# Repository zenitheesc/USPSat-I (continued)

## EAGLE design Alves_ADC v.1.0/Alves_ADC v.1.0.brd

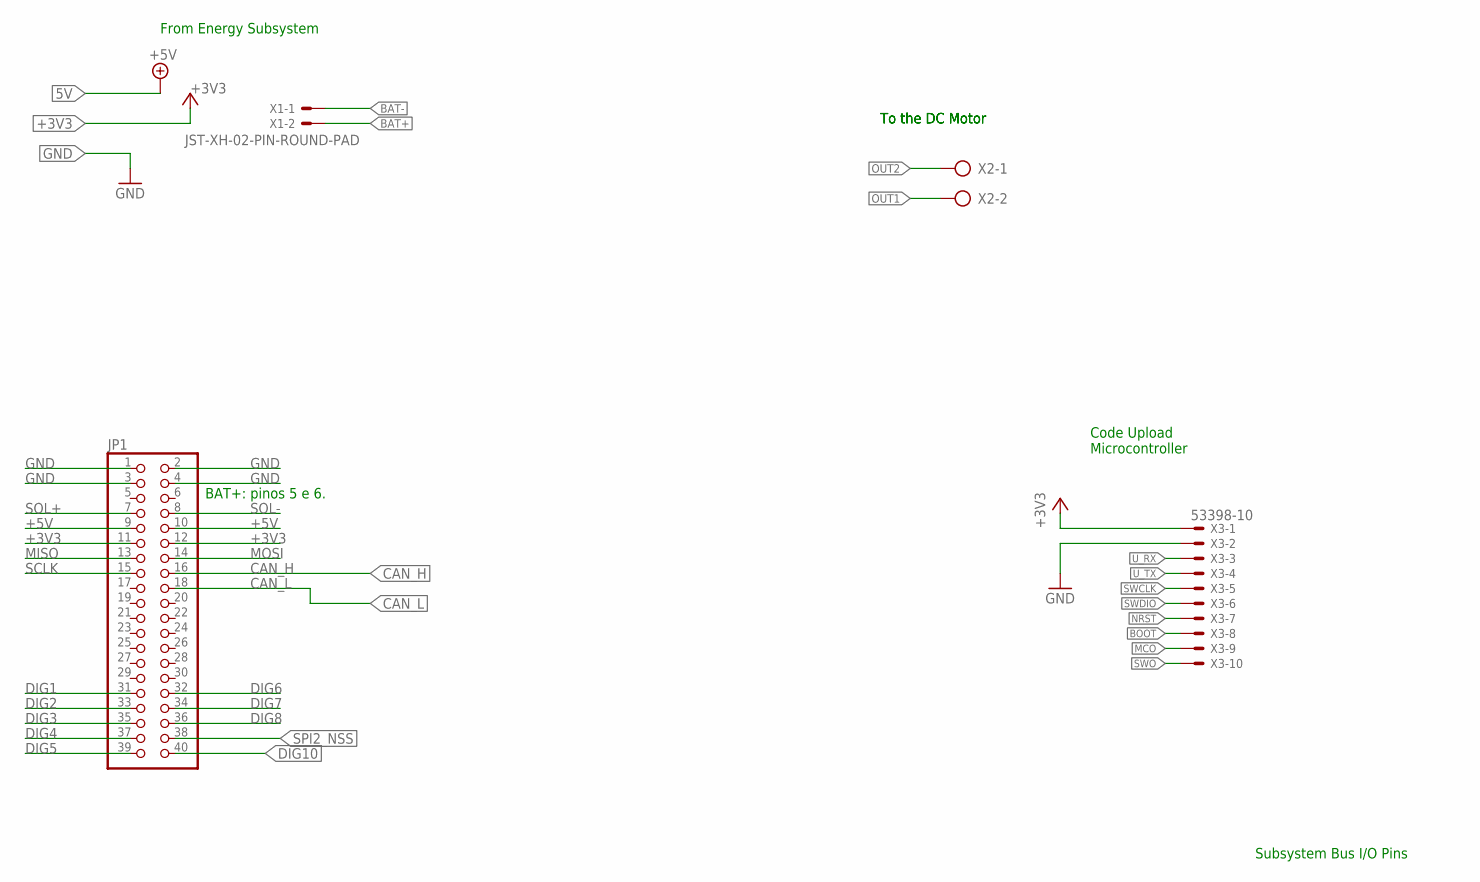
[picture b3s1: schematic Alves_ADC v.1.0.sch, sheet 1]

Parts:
JP1: PINHD-2X20; 2X20
X1: JST-XH-02-PIN-ROUND-PAD; JST-XH-02-PACKAGE-ROUND-PAD
X2: AK500/2
X3: 53398-10

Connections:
+3V3: JP1.11, JP1.12, X3.1; also elsewhere on the board
+5V: JP1.9, JP1.10; also elsewhere on the board
BAT+: X1.2; also elsewhere on the board
BAT-: X1.1; also elsewhere on the board
BOOT: X3.8; also elsewhere on the board
CAN_H: JP1.16; also elsewhere on the board
CAN_L: JP1.18; also elsewhere on the board
DIG1: JP1.31
DIG2: JP1.33
DIG3: JP1.35
DIG4: JP1.37
DIG5: JP1.39
DIG6: JP1.32
DIG7: JP1.34
DIG8: JP1.36
DIG10: JP1.40; also elsewhere on the board
GND: JP1.1, JP1.2, JP1.3, JP1.4, X3.2; also elsewhere on the board
MCO: X3.9; also elsewhere on the board
MISO: JP1.13; also elsewhere on the board
MOSI: JP1.14; also elsewhere on the board
NRST: X3.7; also elsewhere on the board
OUT1: X2.2; also elsewhere on the board
OUT2: X2.1; also elsewhere on the board
SCLK: JP1.15; also elsewhere on the board
SOL+: JP1.7
SOL-: JP1.8
SPI2_NSS: JP1.38; also elsewhere on the board
SWCLK: X3.5; also elsewhere on the board
SWDIO: X3.6; also elsewhere on the board
SWO: X3.10; also elsewhere on the board
U_RX: X3.3; also elsewhere on the board
U_TX: X3.4; also elsewhere on the board

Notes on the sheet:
Subsystem Bus I/O Pins
From Energy Subsystem
To the DC Motor
Code Upload Microcontroller
BAT+: pinos 5 e 6.

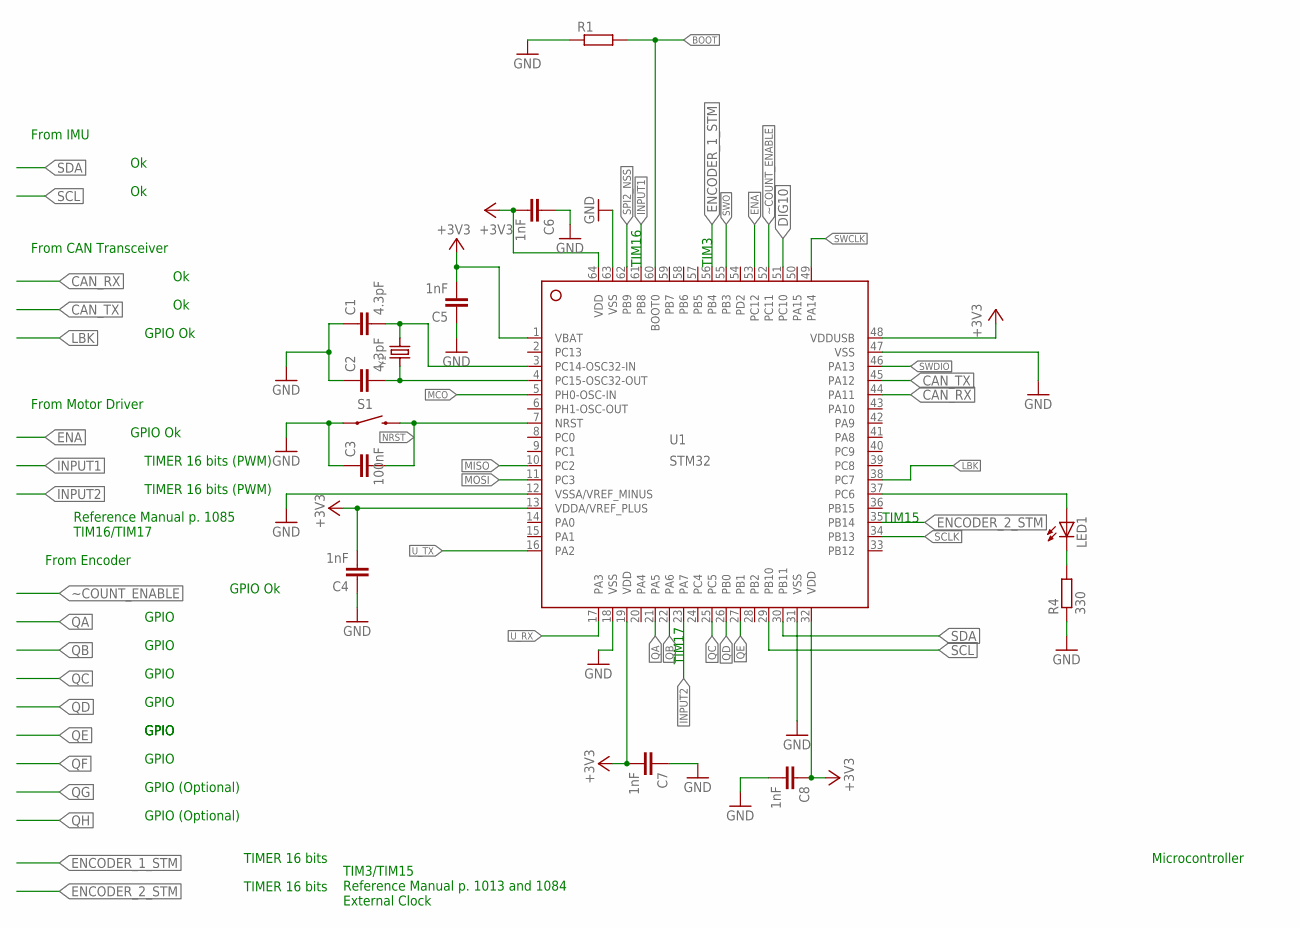
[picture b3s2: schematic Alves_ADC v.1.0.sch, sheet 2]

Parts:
C1, C2: 4.3pF; C1206
C3: 100nF; C1206
C4, C5, C6, C7, C8: 1nF; C1206
LED1: LEDSMT1206; 1206
R1: R-EU_R1206; R1206
R4: 330; R1206
S1: SWITCH-MOMENTARY-2SMD-1101NE; TACTILE-SWITCH-1101NE
U1: STM32; LQFP64_10X10
Y1: CRYSTAL8X3.8SMT; CRYSTAL_8X3.8

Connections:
+3V3: C4.2, C5.2, C6.2, C7.2, C8.1, U1.1 (VBAT), U1.13 (VDDA/VREF_PLUS), U1.19 (VDD), U1.32 (VDD), U1.48 (VDDUSB), U1.64 (VDD); also elsewhere on the board
BOOT: R1.2, U1.60 (BOOT0); also elsewhere on the board
CAN_RX: U1.44 (PA11); also elsewhere on the board
CAN_TX: U1.45 (PA12); also elsewhere on the board
DIG10: U1.51 (PC10); also elsewhere on the board
ENA: U1.53 (PC12); also elsewhere on the board
ENCODER_1_STM: U1.56 (PB4); also elsewhere on the board
ENCODER_2_STM: U1.35 (PB14); also elsewhere on the board
GND: C1.1, C2.1, C3.1, C4.1, C5.1, C6.1, C7.1, C8.2, R1.1, R4.1, S1.1, U1.12 (VSSA/VREF_MINUS), U1.18 (VSS), U1.31 (VSS), U1.47 (VSS), U1.63 (VSS); also elsewhere on the board
INPUT1: U1.61 (PB8); also elsewhere on the board
INPUT2: U1.23 (PA7); also elsewhere on the board
LBK: U1.38 (PC7); also elsewhere on the board
MCO: U1.5 (PH0-OSC-IN); also elsewhere on the board
MISO: U1.10 (PC2); also elsewhere on the board
MOSI: U1.11 (PC3); also elsewhere on the board
unnamed: LED1.A, U1.37 (PC6)
unnamed: C1.2, U1.3 (PC14-OSC32-IN), Y1.P$4 (2)
unnamed: C2.2, U1.4 (PC15-OSC32-OUT), Y1.P$1 (1)
unnamed: LED1.C, R4.2
NRST: C3.2, S1.2, U1.7 (NRST); also elsewhere on the board
QA: U1.21 (PA5); also elsewhere on the board
QB: U1.22 (PA6); also elsewhere on the board
QC: U1.25 (PC5); also elsewhere on the board
QD: U1.26 (PB0); also elsewhere on the board
QE: U1.27 (PB1); also elsewhere on the board
SCL: U1.29 (PB10); also elsewhere on the board
SCLK: U1.34 (PB13); also elsewhere on the board
SDA: U1.30 (PB11); also elsewhere on the board
SPI2_NSS: U1.62 (PB9); also elsewhere on the board
SWCLK: U1.49 (PA14); also elsewhere on the board
SWDIO: U1.46 (PA13); also elsewhere on the board
SWO: U1.55 (PB3); also elsewhere on the board
U_RX: U1.17 (PA3); also elsewhere on the board
U_TX: U1.16 (PA2); also elsewhere on the board
~COUNT_ENABLE: U1.52 (PC11); also elsewhere on the board

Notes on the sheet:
Microcontroller
From IMU
From Motor Driver
From CAN Transceiver
From Encoder
GPIO Ok
TIMER 16 bits (PWM)
TIMER 16 bits
GPIO (Optional)
Reference Manual p. 1085 TIM16/TIM17
TIM3/TIM15 Reference Manual p. 1013 and 1084 External Clock
TIM15
TIM17
TIM16
TIM3
GPIO

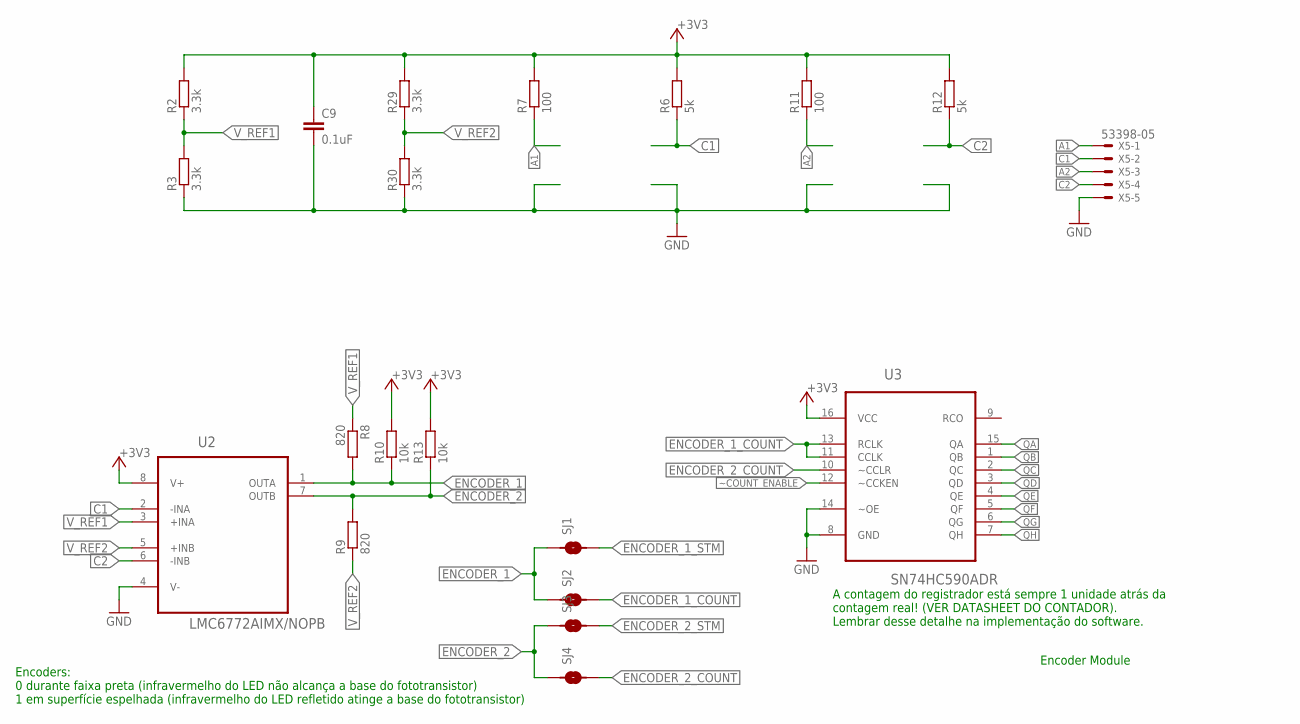
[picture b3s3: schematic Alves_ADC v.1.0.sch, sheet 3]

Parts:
C9: 0.1uF; C1206
R2, R3, R29, R30: 3.3k; R1206
R6, R12: 5k; R1206
R7, R11: 100; R1206
R8, R9: 820; R1206
R10, R13: 10k; R1206
SJ1, SJ2, SJ3, SJ4: SMD-JUMPER-2
U2: LMC6772AIMX/NOPB; SOIC127P600X175-8N
U3: SN74HC590ADR; SOIC127P600X175-16N
X5: 53398-05

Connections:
+3V3: C9.1, R2.2, R6.2, R7.2, R10.2, R11.2, R12.2, R13.2, R29.2, U2.8 (V+), U3.16 (VCC); also elsewhere on the board
A1: R7.1, X5.1
A2: R11.1, X5.3
C1: R6.1, U2.2 (-INA), X5.2
C2: R12.1, U2.6 (-INB), X5.4
ENCODER_1: R8.2, R10.1, SJ1.1, SJ2.1, U2.1 (OUTA)
ENCODER_1_COUNT: SJ2.2, U3.11 (CCLK), U3.13 (RCLK)
ENCODER_1_STM: SJ1.2; also elsewhere on the board
ENCODER_2: R9.2, R13.1, SJ3.1, SJ4.1, U2.7 (OUTB)
ENCODER_2_COUNT: SJ4.2, U3.10 (~CCLR)
ENCODER_2_STM: SJ3.2; also elsewhere on the board
GND: C9.2, R3.1, R30.1, U2.4 (V-), U3.8 (GND), U3.14 (~OE), X5.5; also elsewhere on the board
QA: U3.15 (QA); also elsewhere on the board
QB: U3.1 (QB); also elsewhere on the board
QC: U3.2 (QC); also elsewhere on the board
QD: U3.3 (QD); also elsewhere on the board
QE: U3.4 (QE); also elsewhere on the board
QF: U3.5 (QF)
QG: U3.6 (QG)
QH: U3.7 (QH)
V_REF1: R2.1, R3.2, R8.1, U2.3 (+INA)
V_REF2: R9.1, R29.1, R30.2, U2.5 (+INB)
~COUNT_ENABLE: U3.12 (~CCKEN); also elsewhere on the board

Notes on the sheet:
Encoder Module
Encoders: 0 durante faixa preta (infravermelho do LED não alcança a base do fototransistor) 1 em superfície espelhada (infravermelho do LED refletido atinge a base do fototransistor)
A contagem do registrador está sempre 1 unidade atrás da contagem real! (VER DATASHEET DO CONTADOR). Lembrar desse detalhe na implementação do software.

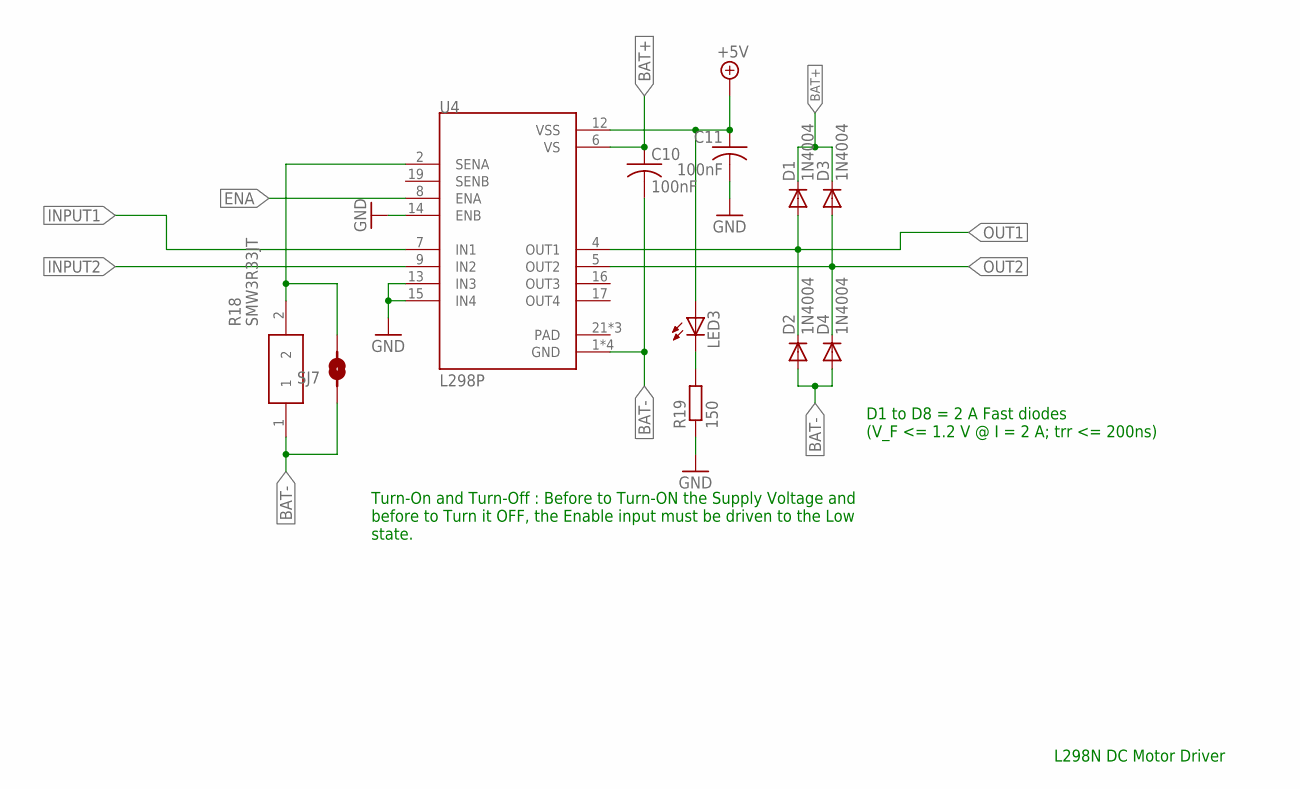
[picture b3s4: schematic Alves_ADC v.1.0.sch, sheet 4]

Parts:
C10, C11: 100nF; C050-024X044
D1, D2, D3, D4: 1N4004; DO41-10
LED3: LEDSMT1206; 1206
R18: SMW3R33JT; RESM12055X530N
R19: 150; R1206
SJ7: SMD-JUMPER-2
U4: L298P; SOIC127P1420X360-20N

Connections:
+5V: C11.1, LED3.A, U4.12 (VSS); also elsewhere on the board
BAT+: C10.1, D1.C, D3.C, U4.6 (VS); also elsewhere on the board
BAT-: C10.2, D2.A, D4.A, R18.1, SJ7.1, U4.1 (GND), U4.10 (GND), U4.11 (GND), U4.20 (GND); also elsewhere on the board
ENA: U4.8 (ENA); also elsewhere on the board
GND: C11.2, R19.1, U4.13 (IN3), U4.14 (ENB), U4.15 (IN4); also elsewhere on the board
INPUT1: U4.7 (IN1); also elsewhere on the board
INPUT2: U4.9 (IN2); also elsewhere on the board
unnamed: LED3.C, R19.2
unnamed: R18.2, SJ7.2, U4.2 (SENA)
OUT1: D1.A, D2.C, U4.4 (OUT1); also elsewhere on the board
OUT2: D3.A, D4.C, U4.5 (OUT2); also elsewhere on the board

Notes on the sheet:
L298N DC Motor Driver
D1 to D8 = 2 A Fast diodes (V_F <= 1.2 V @ I = 2 A; trr <= 200ns)
Turn-On and Turn-Off : Before to Turn-ON the Supply Voltage and before to Turn it OFF, the Enable input must be driven to the Low state.

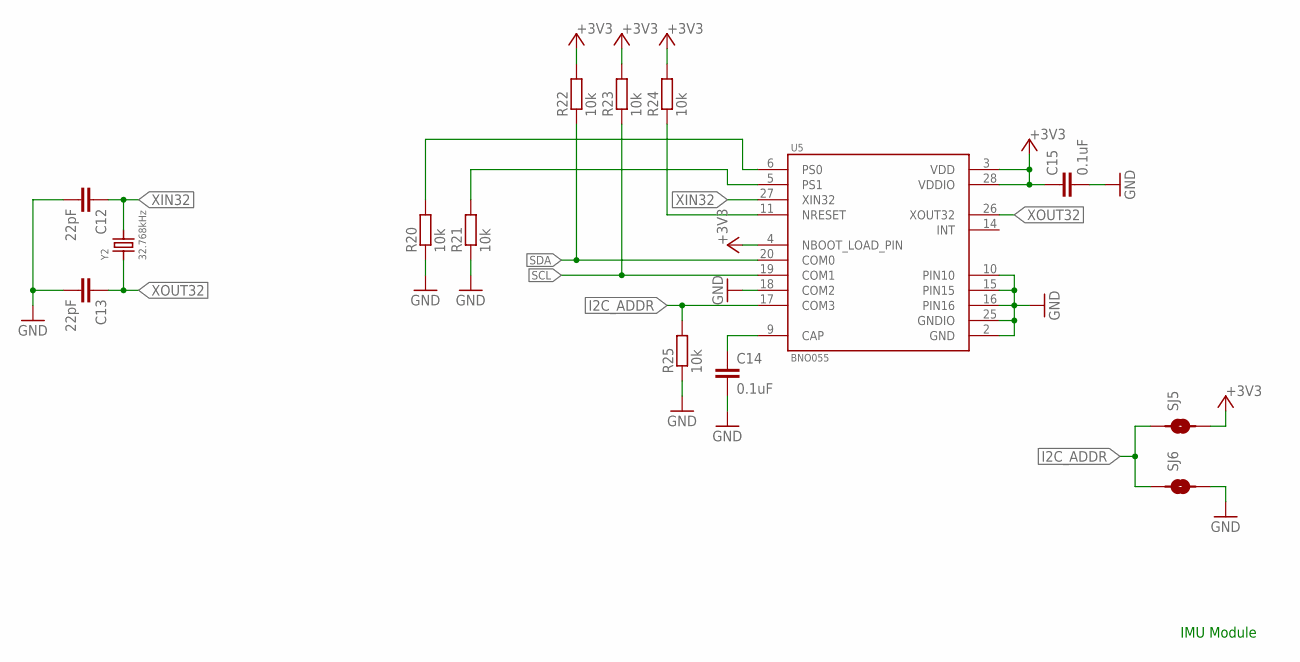
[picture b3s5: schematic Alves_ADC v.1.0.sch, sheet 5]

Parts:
C12, C13: 22pF; C1206
C14, C15: 0.1uF; C1206
R20, R21, R22, R23, R24, R25: 10k; R1206
SJ5, SJ6: SMD-JUMPER-2
U5: BNO055; LGA28R50P4X10_380X520X100
Y2: 32.768kHz; CRYSTAL_8X3.8

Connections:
+3V3: C15.1, R22.2, R23.2, R24.2, SJ5.2, U5.3 (VDD), U5.4 (NBOOT_LOAD_PIN), U5.28 (VDDIO); also elsewhere on the board
GND: C12.2, C13.2, C14.2, C15.2, R20.1, R21.1, R25.1, SJ6.2, U5.2 (GND), U5.10 (PIN10), U5.15 (PIN15), U5.16 (PIN16), U5.18 (COM2), U5.25 (GNDIO); also elsewhere on the board
I2C_ADDR: R25.2, SJ5.1, SJ6.1, U5.17 (COM3)
unnamed: C14.1, U5.9 (CAP)
NRESET: R24.1, U5.11 (NRESET)
PS0: R20.2, U5.6 (PS0)
PS1: R21.2, U5.5 (PS1)
SCL: R23.1, U5.19 (COM1); also elsewhere on the board
SDA: R22.1, U5.20 (COM0); also elsewhere on the board
XIN32: C12.1, U5.27 (XIN32), Y2.P$4 (2)
XOUT32: C13.1, U5.26 (XOUT32), Y2.P$1 (1)

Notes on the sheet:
IMU Module

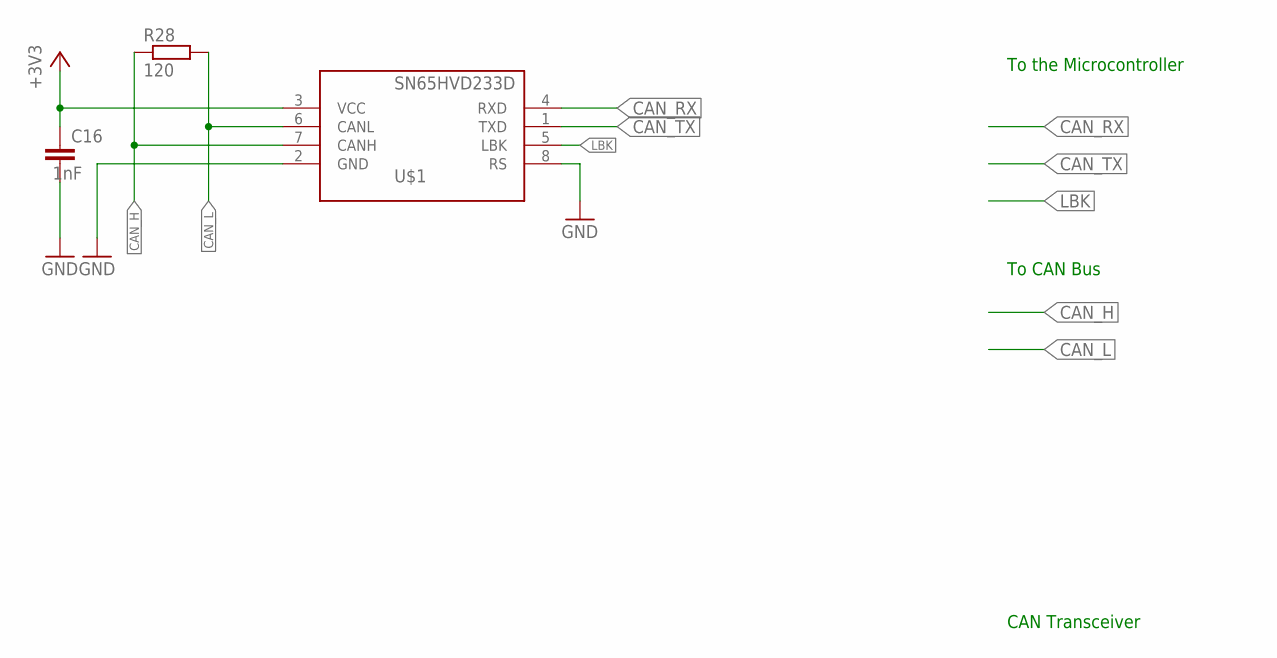
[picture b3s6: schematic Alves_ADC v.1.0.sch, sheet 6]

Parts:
C16: 1nF; C1206
R28: 120; R1206
U$1: SN65HVD233D; SOIC8

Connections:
+3V3: C16.1, U$1.3 (VCC); also elsewhere on the board
CAN_H: R28.1, U$1.7 (CANH); also elsewhere on the board
CAN_L: R28.2, U$1.6 (CANL); also elsewhere on the board
CAN_RX: U$1.4 (RXD); also elsewhere on the board
CAN_TX: U$1.1 (TXD); also elsewhere on the board
GND: C16.2, U$1.2 (GND), U$1.8 (RS); also elsewhere on the board
LBK: U$1.5 (LBK); also elsewhere on the board

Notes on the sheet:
CAN Transceiver
To the Microcontroller
To CAN Bus

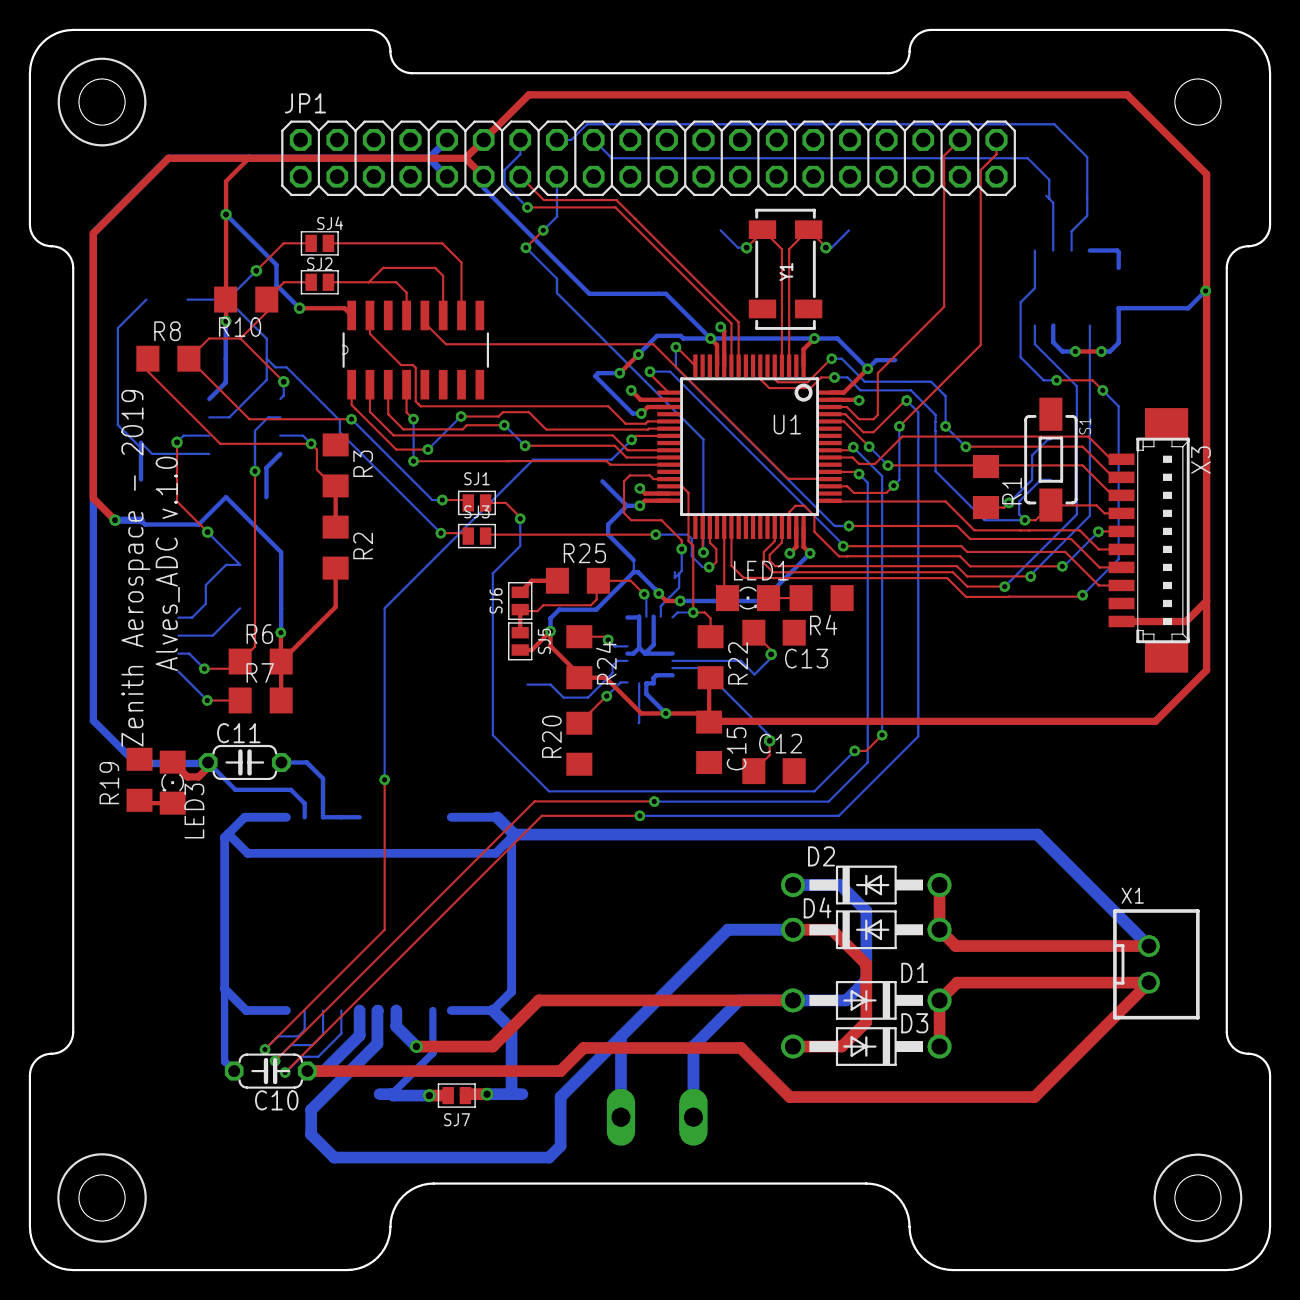
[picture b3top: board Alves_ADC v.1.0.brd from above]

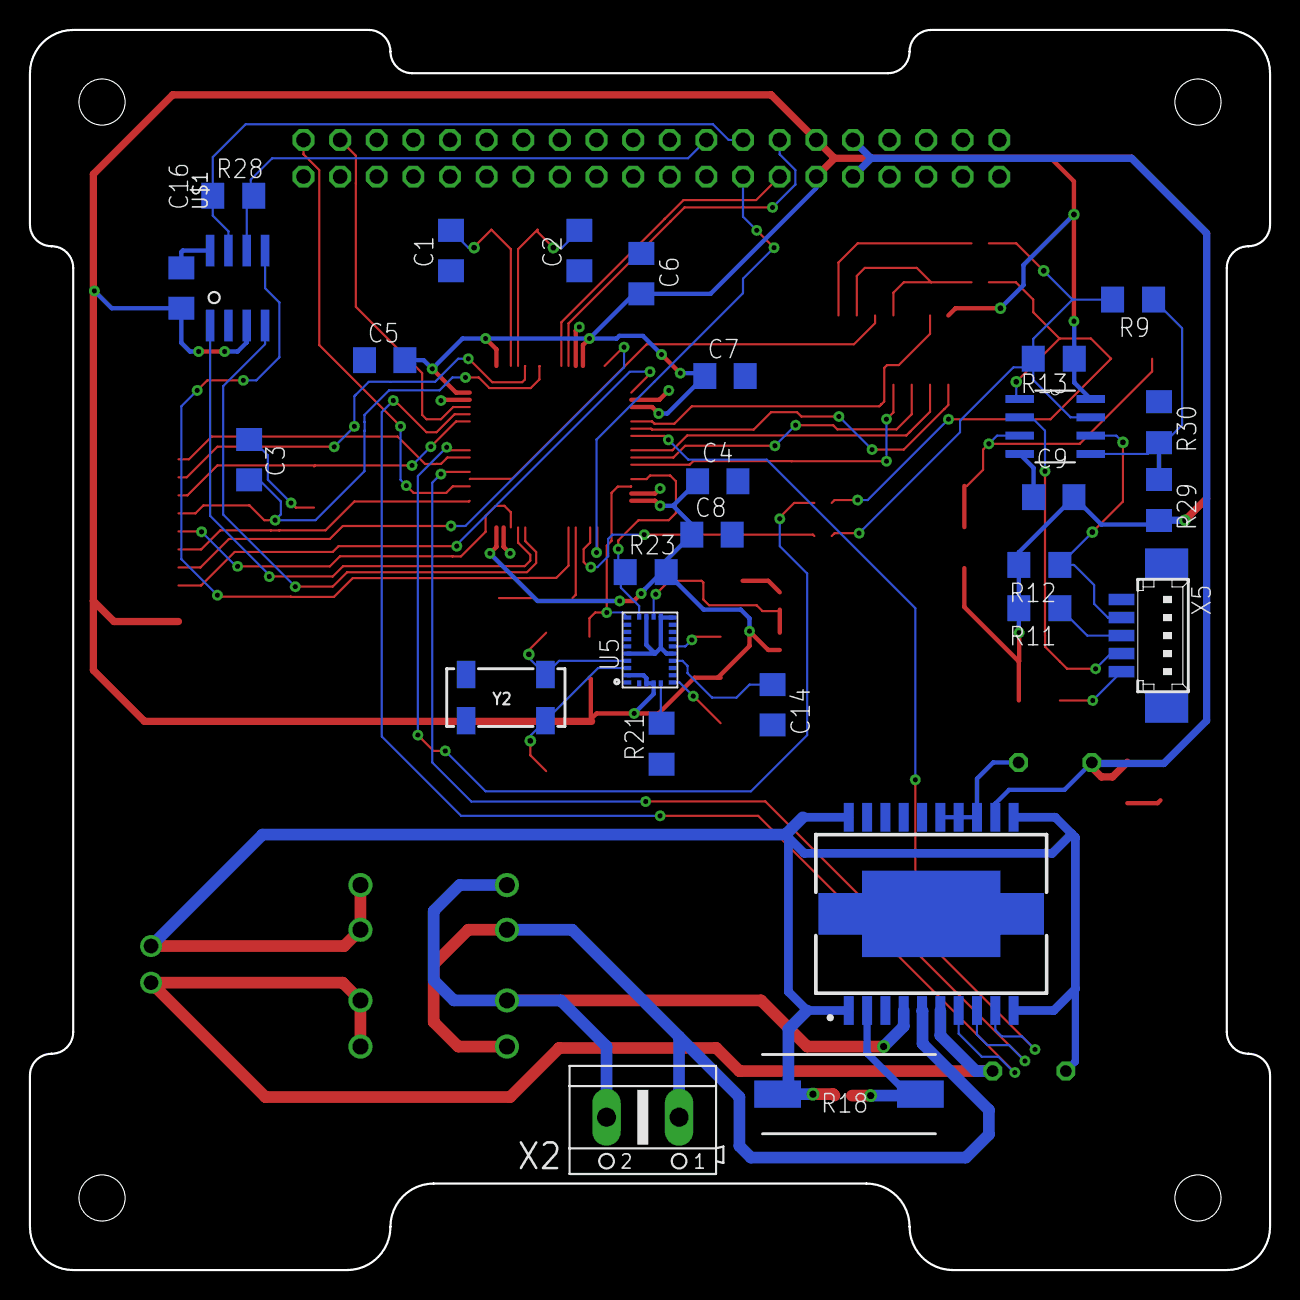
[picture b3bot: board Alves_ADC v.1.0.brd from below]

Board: 2 copper layers, 86.0 x 86.0 mm, 66 parts (28 on the bottom side), 61 nets.

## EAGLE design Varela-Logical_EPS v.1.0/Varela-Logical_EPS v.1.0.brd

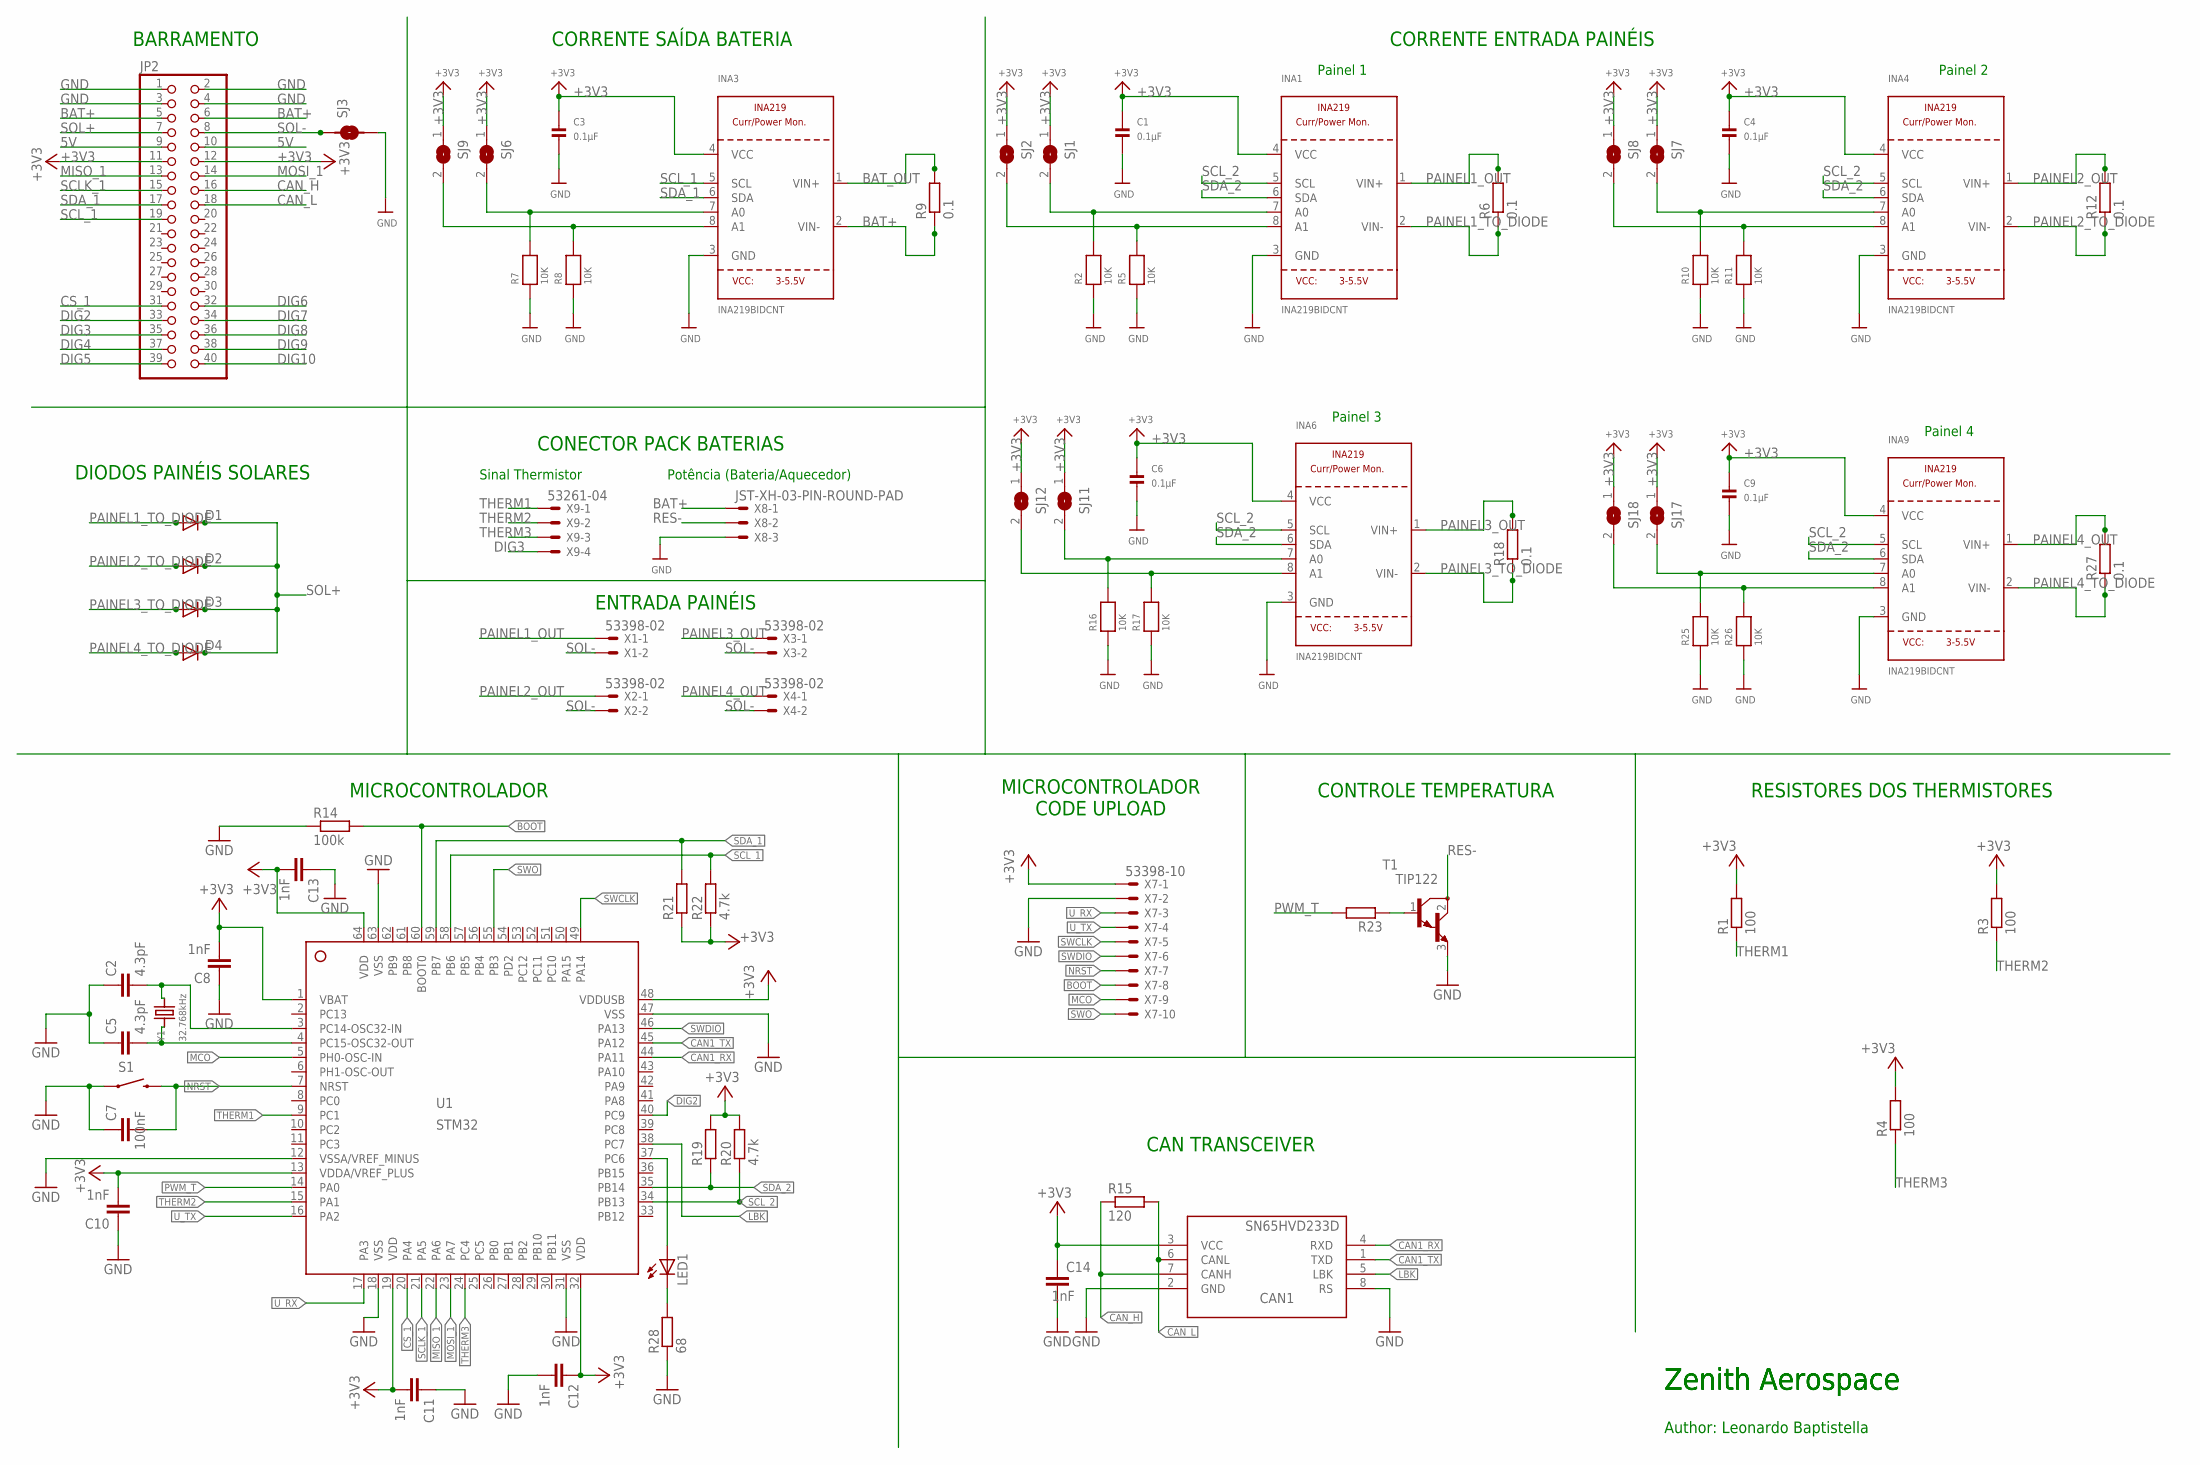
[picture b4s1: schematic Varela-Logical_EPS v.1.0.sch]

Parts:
C1, C3, C4, C6, C9: 0.1µF; 1206
C2, C5: 4.3pF; C1206
C7: 100nF; C1206
C8, C10, C11, C12, C13, C14: 1nF; C1206
CAN1: SN65HVD233D; SOIC8
D1, D2, D3, D4: DIODE-DO-214AC; DO-214AC
INA1, INA3, INA4, INA6, INA9: INA219BIDCNT; SOT23-8
JP2: PINHD-2X20; 2X20
LED1: LEDSMT1206; 1206
R1, R3, R4: 100; R1206
R2, R5, R7, R8, R10, R11, R16, R17, R25, R26: 10K; 1206
R6, R9, R12, R18, R27: 0.1; R2512
R14: 100k; R1206
R15: 120; R1206
R19, R20, R21, R22: 4.7k; R1206
R23: R-EU_R1206; R1206
R28: 68; R1206
S1: SWITCH-MOMENTARY-2SMD-1101NE; TACTILE-SWITCH-1101NE
SJ1, SJ2, SJ6, SJ7, SJ8, SJ9, SJ11, SJ12, SJ17, SJ18: SOLDERJUMPERREFLOW_NOPASTE; SOLDERJUMPER_REFLOW_NOPASTE
SJ3: SMD-JUMPER-2
T1: TIP122; TO220
U1: STM32; LQFP64_10X10
X1, X2, X3, X4: 53398-02
X7: 53398-10
X8: JST-XH-03-PIN-ROUND-PAD; JST-XH-03-PACKAGE-ROUND-PAD
X9: 53261-04
Y1: 32.768kHz; CRYSTAL_8X3.8

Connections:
5V: JP2.9, JP2.10
+3V3: C1.1, C3.1, C4.1, C6.1, C8.2, C9.1, C10.2, C11.2, C12.1, C13.2, C14.1, CAN1.3 (VCC), INA1.4 (VCC), INA3.4 (VCC), INA4.4 (VCC), INA6.4 (VCC), INA9.4 (VCC), JP2.11, JP2.12, R1.2, R3.2, R4.2, R19.2, R20.2, R21.1, R22.1, SJ1.1, SJ2.1, SJ6.1, SJ7.1, SJ8.1, SJ9.1, SJ11.1, SJ12.1, SJ17.1, SJ18.1, U1.1 (VBAT), U1.13 (VDDA/VREF_PLUS), U1.19 (VDD), U1.32 (VDD), U1.48 (VDDUSB), U1.64 (VDD), X7.1
BAT+: INA3.2 (VIN-), JP2.5, JP2.6, R9.1, X8.1
BAT_OUT: INA3.1 (VIN+), R9.2
BOOT: R14.2, U1.60 (BOOT0), X7.8
CAN1_RX: CAN1.4 (RXD), U1.44 (PA11)
CAN1_TX: CAN1.1 (TXD), U1.45 (PA12)
CAN_H: CAN1.7 (CANH), JP2.16, R15.1
CAN_L: CAN1.6 (CANL), JP2.18, R15.2
CS_1: JP2.31, U1.20 (PA4)
DIG2: JP2.33, U1.40 (PC9)
DIG3: JP2.35, X9.4
DIG4: JP2.37
DIG5: JP2.39
DIG6: JP2.32
DIG7: JP2.34
DIG8: JP2.36
DIG9: JP2.38
DIG10: JP2.40
GND: C1.2, C2.1, C3.2, C4.2, C5.1, C6.2, C7.1, C8.1, C9.2, C10.1, C11.1, C12.2, C13.1, C14.2, CAN1.2 (GND), CAN1.8 (RS), INA1.3 (GND), INA3.3 (GND), INA4.3 (GND), INA6.3 (GND), INA9.3 (GND), JP2.1, JP2.2, JP2.3, JP2.4, R2.1, R5.1, R7.1, R8.1, R10.1, R11.1, R14.1, R16.1, R17.1, R25.1, R26.1, R28.1, S1.1, SJ3.2, T1.3 (E), U1.12 (VSSA/VREF_MINUS), U1.18 (VSS), U1.31 (VSS), U1.47 (VSS), U1.63 (VSS), X7.2, X8.3
LBK: CAN1.5 (LBK), U1.38 (PC7)
MCO: U1.5 (PH0-OSC-IN), X7.9
MISO_1: JP2.13, U1.22 (PA6)
MOSI_1: JP2.14, U1.23 (PA7)
unnamed: C2.2, U1.3 (PC14-OSC32-IN), Y1.P$4 (2)
unnamed: R23.1, T1.1 (B)
unnamed: C5.2, U1.4 (PC15-OSC32-OUT), Y1.P$1 (1)
unnamed: INA1.8 (A1), R5.2, SJ2.2
unnamed: INA1.7 (A0), R2.2, SJ1.2
unnamed: INA3.8 (A1), R8.2, SJ9.2
unnamed: INA3.7 (A0), R7.2, SJ6.2
unnamed: INA4.8 (A1), R11.2, SJ8.2
unnamed: INA4.7 (A0), R10.2, SJ7.2
unnamed: LED1.A, U1.37 (PC6)
unnamed: LED1.C, R28.2
unnamed: INA6.8 (A1), R17.2, SJ12.2
unnamed: INA6.7 (A0), R16.2, SJ11.2
unnamed: INA9.8 (A1), R26.2, SJ18.2
unnamed: INA9.7 (A0), R25.2, SJ17.2
NRST: C7.2, S1.2, U1.7 (NRST), X7.7
PAINEL1_OUT: INA1.1 (VIN+), R6.2, X1.1
PAINEL1_TO_DIODE: D1.A, INA1.2 (VIN-), R6.1
PAINEL2_OUT: INA4.1 (VIN+), R12.2, X2.1
PAINEL2_TO_DIODE: D2.A, INA4.2 (VIN-), R12.1
PAINEL3_OUT: INA6.1 (VIN+), R18.2, X3.1
PAINEL3_TO_DIODE: D3.A, INA6.2 (VIN-), R18.1
PAINEL4_OUT: INA9.1 (VIN+), R27.2, X4.1
PAINEL4_TO_DIODE: D4.A, INA9.2 (VIN-), R27.1
PWM_T: R23.2, U1.14 (PA0)
RES-: T1.2 (C), X8.2
SCLK_1: JP2.15, U1.21 (PA5)
SCL_1: INA3.5 (SCL), JP2.19, R22.2, U1.58 (PB6)
SCL_2: INA1.5 (SCL), INA4.5 (SCL), INA6.5 (SCL), INA9.5 (SCL), R20.1, U1.34 (PB13)
SDA_1: INA3.6 (SDA), JP2.17, R21.2, U1.59 (PB7)
SDA_2: INA1.6 (SDA), INA4.6 (SDA), INA6.6 (SDA), INA9.6 (SDA), R19.1, U1.35 (PB14)
SOL+: D1.C, D2.C, D3.C, D4.C, JP2.7
SOL-: JP2.8, SJ3.1, X1.2, X2.2, X3.2, X4.2
SWCLK: U1.49 (PA14), X7.5
SWDIO: U1.46 (PA13), X7.6
SWO: U1.55 (PB3), X7.10
THERM1: R1.1, U1.9 (PC1), X9.1
THERM2: R3.1, U1.15 (PA1), X9.2
THERM3: R4.1, U1.24 (PC4), X9.3
U_RX: U1.17 (PA3), X7.3
U_TX: U1.16 (PA2), X7.4

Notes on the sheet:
ENTRADA PAINÉIS
BARRAMENTO
CORRENTE ENTRADA PAINÉIS
CORRENTE SAÍDA BATERIA
Painel 1
Painel 2
Painel 3
Painel 4
DIODOS PAINÉIS SOLARES
CONECTOR PACK BATERIAS
Sinal Thermistor
Potência (Bateria/Aquecedor)
RESISTORES DOS THERMISTORES
CONTROLE TEMPERATURA
Author: Leonardo Baptistella
Zenith Aerospace
MICROCONTROLADOR
MICROCONTROLADOR CODE UPLOAD
CAN TRANSCEIVER

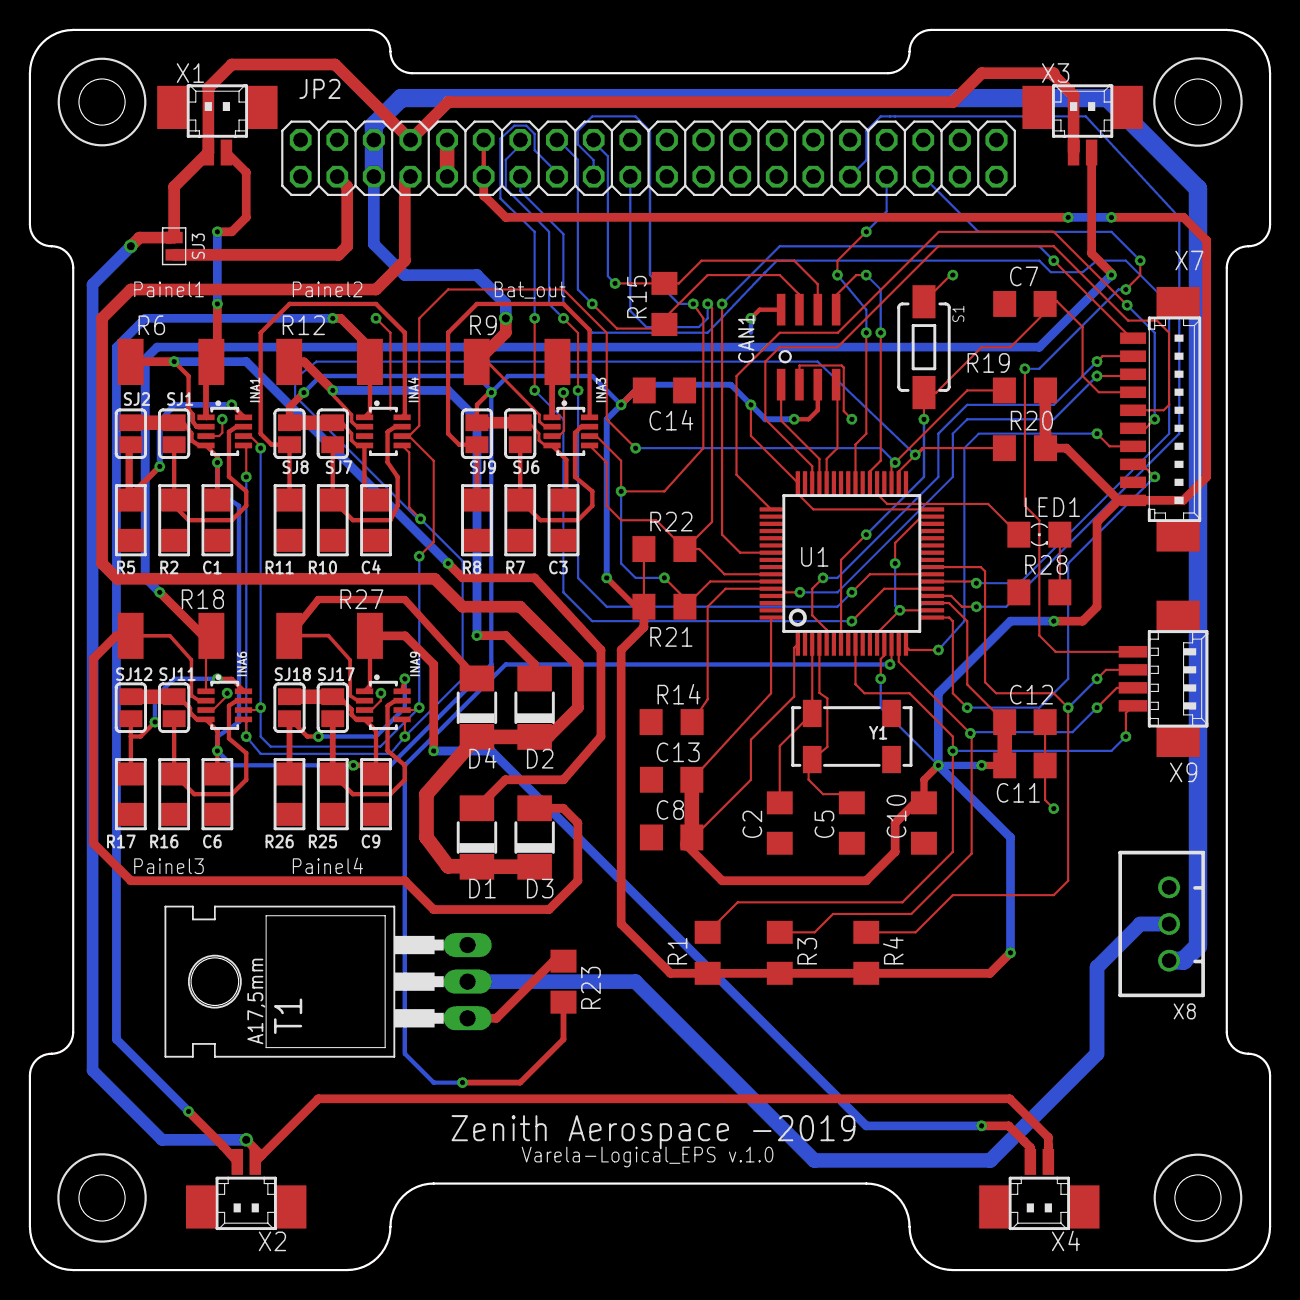
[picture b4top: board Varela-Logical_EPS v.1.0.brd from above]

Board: 2 copper layers, 86.0 x 86.0 mm, 74 parts (0 on the bottom side), 58 nets.
